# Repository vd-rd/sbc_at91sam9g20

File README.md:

# Microchip AT91SAM9G20

## Description
 The follow-up to my previous [SBC based on AT91SAM9260](https://github.com/vd-rd/sbc_at91sam9260), enhancing the board specs in computing power and flexibility. The board is smaller 60x40mm now (SAM9260 was 80x40mm) while keeping the same amount of supported RAM and interfaces. AT91SAM9G20 boosts core speed to 400MHz and bus speed to 133MHz.
 
Board overview (draft):
[TBD]

### Features

| Characteristic | Description |
| --- | --- |
| Dimensions | 60mm x 40mm |
| Processor | AT91SAM9G20 - ARM926EJ @ 400MHz |
| Oscillators |  18.432MHz main clock, 32.768kHz RTC |
| RAM | SDRAM 128MB max (2x512Mbit modules) |
| Storage | microSD |
| USB | 1 microUSB client, 2 USB Host|
| Ethernet | RMII header |
| WiFi/BT | N/A |
| Supply | USB 5V, ACIN 5V |

Common interfaces such as I2C, SPI, UART and GPIO are exposed on the header.

### Building and flashing

Build U-Boot and Linux kernel + rootFS - TBD

Flash to SDCard - TBD

### Resources

You can find all necesary information to build or evaluate the module here:
   - [Fabrication files](https://github.com/vd-rd/sbc_alw_a13/releases)

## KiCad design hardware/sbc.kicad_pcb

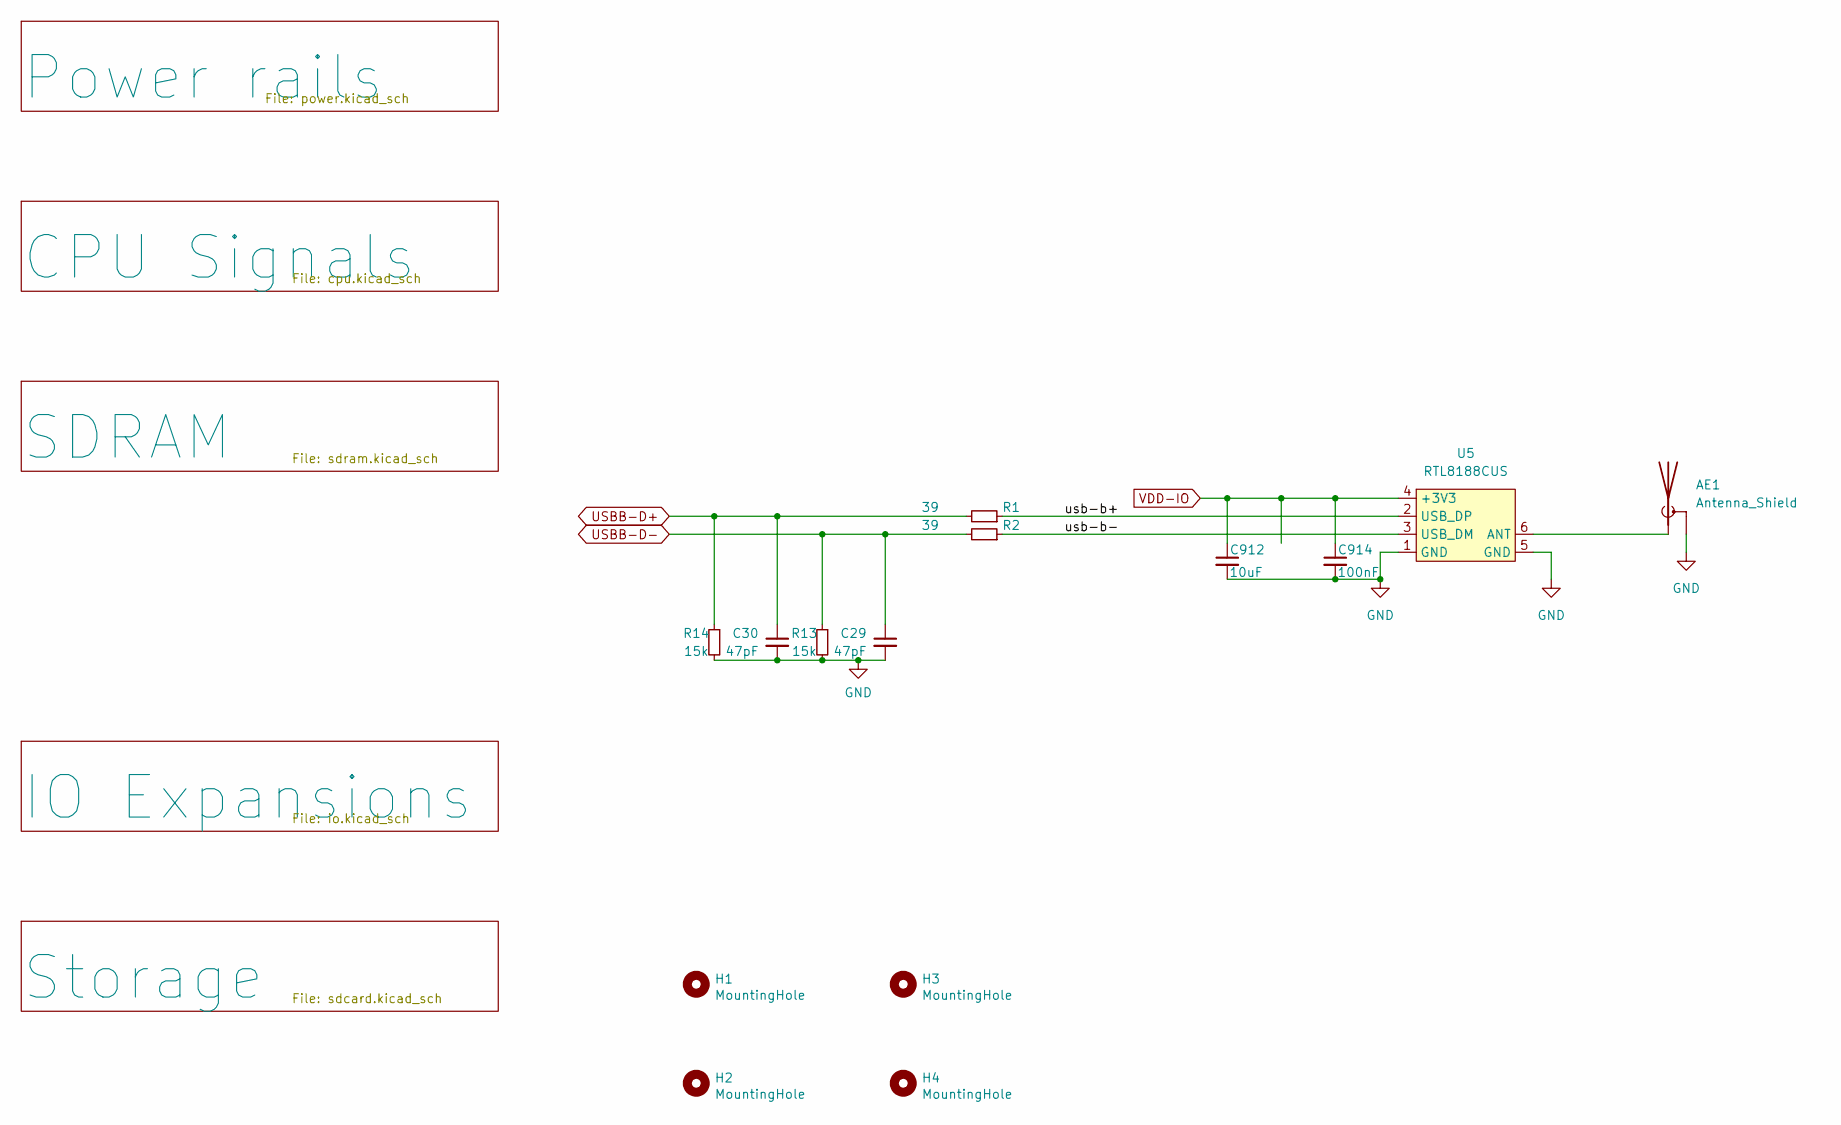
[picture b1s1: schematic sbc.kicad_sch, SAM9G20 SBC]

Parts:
AE1: Antenna_Shield; U.FL_Hirose_U.FL-R-SMT-1_Vertical
C29, C30: 47pF; C_0402_1005Metric
C912: 10uF; C_0603_1608Metric
C914: 100nF; C_0402_1005Metric
H1, H2, H3, H4: MountingHole; MountingHole_2.7mm_M2.5_DIN965
R1, R2: 39; R_0402_1005Metric
R13, R14: 15k; R_0402_1005Metric
U5: RTL8188CUS

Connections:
/usb-b+: R1.1, U5.2 (USB_DP)
/usb-b-: R2.1, U5.3 (USB_DM)
GND: AE1.2 (Shield), C29.2, C30.2, C912.2, C914.2, R13.2, R14.2, U5.1 (GND), U5.5 (GND); also elsewhere on the board
unnamed: AE1.1 (A), U5.6 (ANT)
USBB-D+: C30.1, R1.2, R14.1; also elsewhere on the board
USBB-D-: C29.1, R2.2, R13.1; also elsewhere on the board
VDD-IO: C912.1, C914.1, U5.4 (+3V3); also elsewhere on the board

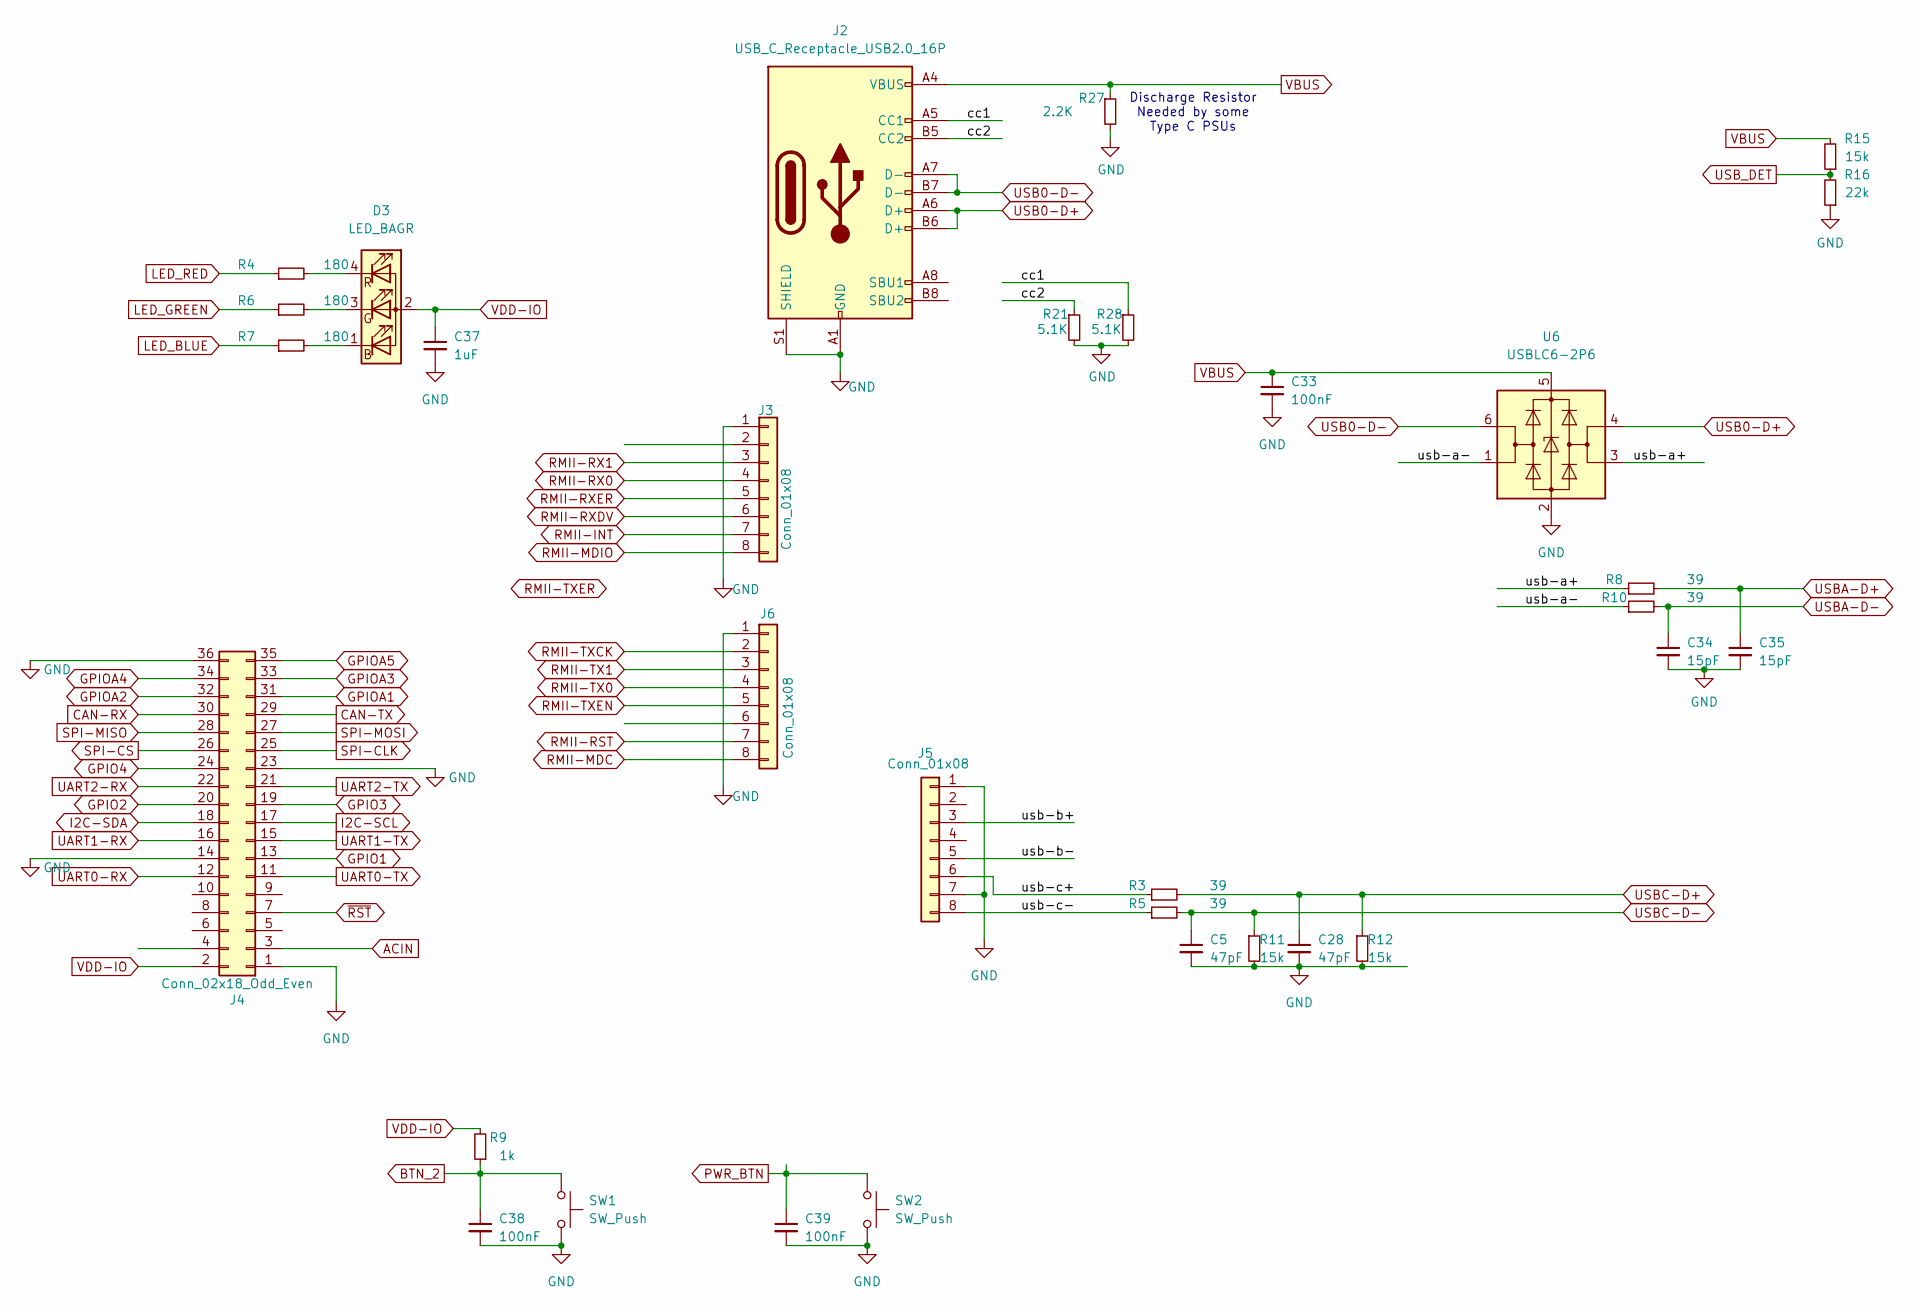
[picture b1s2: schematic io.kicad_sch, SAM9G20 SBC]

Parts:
C5, C28: 47pF; C_0402_1005Metric
C33, C38, C39: 100nF; C_0402_1005Metric
C34, C35: 15pF; C_0402_1005Metric
C37: 1uF; C_0402_1005Metric
D3: LED_BAGR; LED_RGB_Optosupply_OSTB0805C1E-A-0.8T
J2: USB_C_Receptacle_USB2.0_16P; USB_C_Receptacle_GCT_USB4105-xx-A_16P_TopMnt_Horizontal
J3, J5, J6: Conn_01x08; PinHeader_2x04_P1.27mm_Vertical
J4: Conn_02x18_Odd_Even; PinHeader_2x18_P2.54mm_Vertical
R3, R5, R8, R10: 39; R_0402_1005Metric
R4, R6, R7: 180; R_0402_1005Metric
R9: 1k; R_0402_1005Metric
R11, R12, R15: 15k; R_0402_1005Metric
R16: 22k; R_0402_1005Metric
R21, R28: 5.1K; R_0402_1005Metric; Part Description Resistor 2.2K M1005 1% 63mW
R27: 2.2K; R_0402_1005Metric; Part Description Resistor 2.2K M1005 1% 63mW
SW1, SW2: SW_Push; SW_SPST_EVQP7C
U6: USBLC6-2P6; SOT-23-6

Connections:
/IO Expansions/cc1: J2.A5 (CC1), R28.1
/IO Expansions/cc2: J2.B5 (CC2), R21.1
/IO Expansions/usb-a+: R8.1, U6.3 (I/O2)
/IO Expansions/usb-a-: R10.1, U6.1 (I/O1)
/IO Expansions/usb-b+: J5.3
/IO Expansions/usb-b-: J5.5
/IO Expansions/usb-c+: J5.6, R3.1
/IO Expansions/usb-c-: J5.8, R5.1
ACIN: J4.3; also elsewhere on the board
BTN_2: C38.1, R9.1, SW1.1; also elsewhere on the board
CAN-RX: J4.30
CAN-TX: J4.29
GND: C5.2, C28.2, C33.2, C34.2, C35.2, C37.2, C38.2, C39.2, J2.A1 (GND), J2.A12 (GND), J2.B1 (GND), J2.B12 (GND), J2.S1 (SHIELD), J3.1, J4.1, J4.14, J4.23, J4.36, J5.1, J5.7, J6.1, R11.2, R12.2, R16.1, R21.2, R27.2, R28.2, SW1.2, SW2.2, U6.2 (GND); also elsewhere on the board
GPIO1: J4.13; also elsewhere on the board
GPIO2: J4.20; also elsewhere on the board
GPIO3: J4.19; also elsewhere on the board
GPIO4: J4.24; also elsewhere on the board
GPIOA1: J4.31; also elsewhere on the board
GPIOA2: J4.32; also elsewhere on the board
GPIOA3: J4.33; also elsewhere on the board
GPIOA4: J4.34; also elsewhere on the board
GPIOA5: J4.35
I2C-SCL: J4.17; also elsewhere on the board
I2C-SDA: J4.18; also elsewhere on the board
LED_BLUE: R7.1; also elsewhere on the board
LED_GREEN: R6.1; also elsewhere on the board
LED_RED: R4.1; also elsewhere on the board
unnamed: D3.1 (BK), R7.2
unnamed: D3.3 (GK), R6.2
unnamed: D3.4 (RK), R4.2
PWR_BTN: C39.1, SW2.1; also elsewhere on the board
RMII-INT: J3.7
RMII-MDC: J6.8; also elsewhere on the board
RMII-MDIO: J3.8; also elsewhere on the board
RMII-RST: J6.7
RMII-RX0: J3.4; also elsewhere on the board
RMII-RX1: J3.3; also elsewhere on the board
RMII-RXDV: J3.6; also elsewhere on the board
RMII-RXER: J3.5; also elsewhere on the board
RMII-TX0: J6.4; also elsewhere on the board
RMII-TX1: J6.3; also elsewhere on the board
RMII-TXCK: J6.2; also elsewhere on the board
RMII-TXEN: J6.5; also elsewhere on the board
SPI-CLK: J4.25; also elsewhere on the board
SPI-CS: J4.26; also elsewhere on the board
SPI-MISO: J4.28; also elsewhere on the board
SPI-MOSI: J4.27; also elsewhere on the board
UART0-RX: J4.12; also elsewhere on the board
UART0-TX: J4.11; also elsewhere on the board
UART1-RX: J4.16; also elsewhere on the board
UART1-TX: J4.15; also elsewhere on the board
UART2-RX: J4.22; also elsewhere on the board
UART2-TX: J4.21; also elsewhere on the board
USB0-D+: J2.A6 (D+), J2.B6 (D+), U6.4 (I/O2)
USB0-D-: J2.A7 (D-), J2.B7 (D-), U6.6 (I/O1)
USBA-D+: C35.1, R8.2; also elsewhere on the board
USBA-D-: C34.1, R10.2; also elsewhere on the board
USBC-D+: C28.1, R3.2, R12.1; also elsewhere on the board
USBC-D-: C5.1, R5.2, R11.1; also elsewhere on the board
USB_DET: R15.1, R16.2; also elsewhere on the board
VBUS: C33.1, J2.A4 (VBUS), J2.A9 (VBUS), J2.B4 (VBUS), J2.B9 (VBUS), R15.2, R27.1, U6.5 (VBUS); also elsewhere on the board
VDD-IO: C37.1, D3.2 (A), J4.2, R9.2; also elsewhere on the board
~RST: J4.7; also elsewhere on the board

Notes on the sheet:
Discharge Resistor Needed by some Type C PSUs

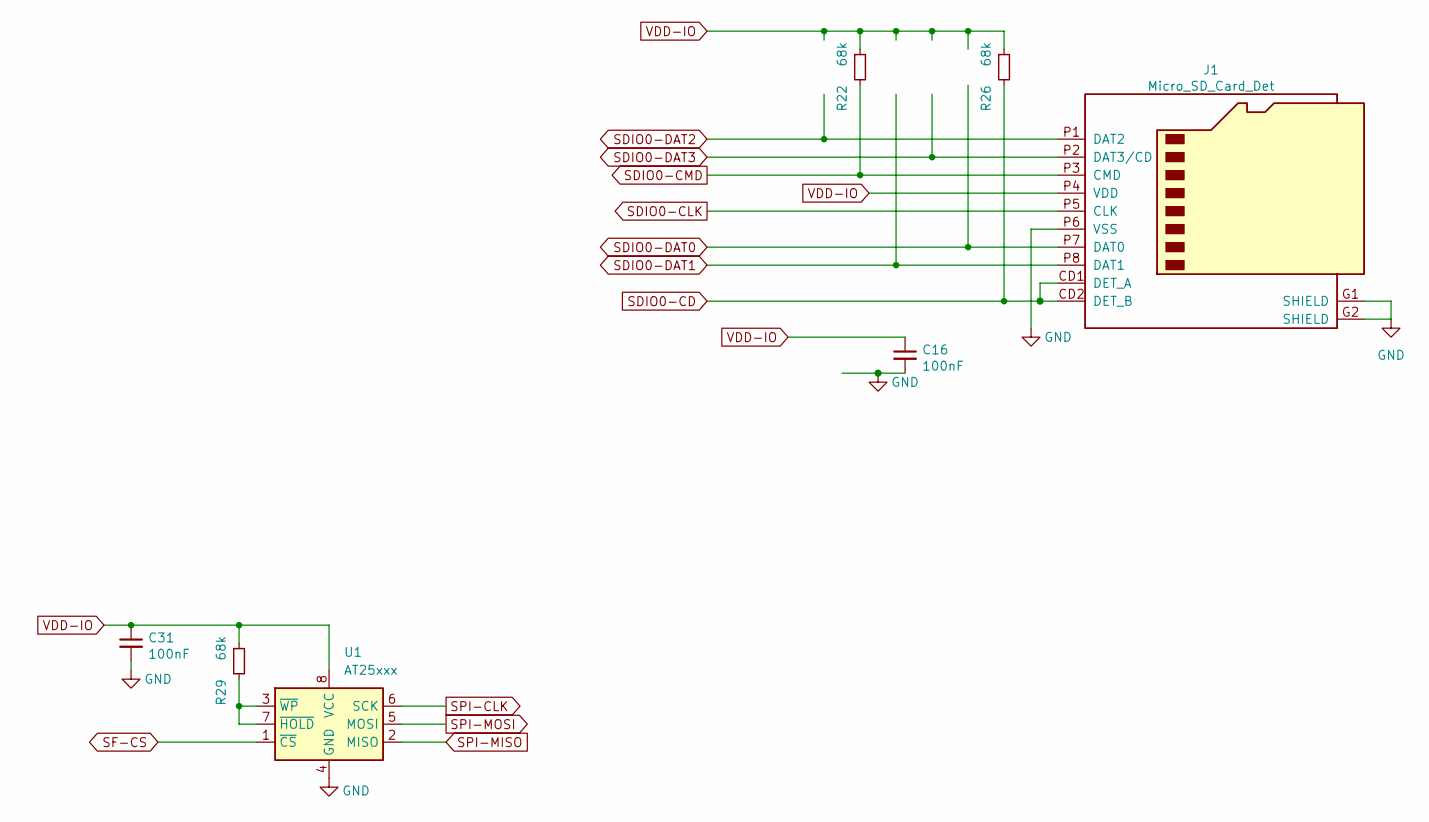
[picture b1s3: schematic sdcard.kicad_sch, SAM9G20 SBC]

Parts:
C16, C31: 100nF; C_0402_1005Metric
J1: Micro_SD_Card_Det; MEM20610118800A
R22, R26, R29: 68k; R_0402_1005Metric
U1: AT25xxx; SOIC-8_5.23x5.23mm_P1.27mm

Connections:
GND: C16.2, C31.2, J1.G1 (SHIELD), J1.G2 (SHIELD), J1.P6 (VSS), U1.4 (GND); also elsewhere on the board
unnamed: R29.2, U1.3 (~WP), U1.7 (~HOLD)
SDIO0-CD: J1.CD1 (DET_A), J1.CD2 (DET_B), R26.2; also elsewhere on the board
SDIO0-CLK: J1.P5 (CLK); also elsewhere on the board
SDIO0-CMD: J1.P3 (CMD), R22.2; also elsewhere on the board
SDIO0-DAT0: J1.P7 (DAT0); also elsewhere on the board
SDIO0-DAT1: J1.P8 (DAT1); also elsewhere on the board
SDIO0-DAT2: J1.P1 (DAT2); also elsewhere on the board
SDIO0-DAT3: J1.P2 (DAT3/CD); also elsewhere on the board
SF-CS: U1.1 (~CS); also elsewhere on the board
SPI-CLK: U1.6 (SCK); also elsewhere on the board
SPI-MISO: U1.2 (MISO); also elsewhere on the board
SPI-MOSI: U1.5 (MOSI); also elsewhere on the board
VDD-IO: C16.1, C31.1, J1.P4 (VDD), R22.1, R26.1, R29.1, U1.8 (VCC); also elsewhere on the board

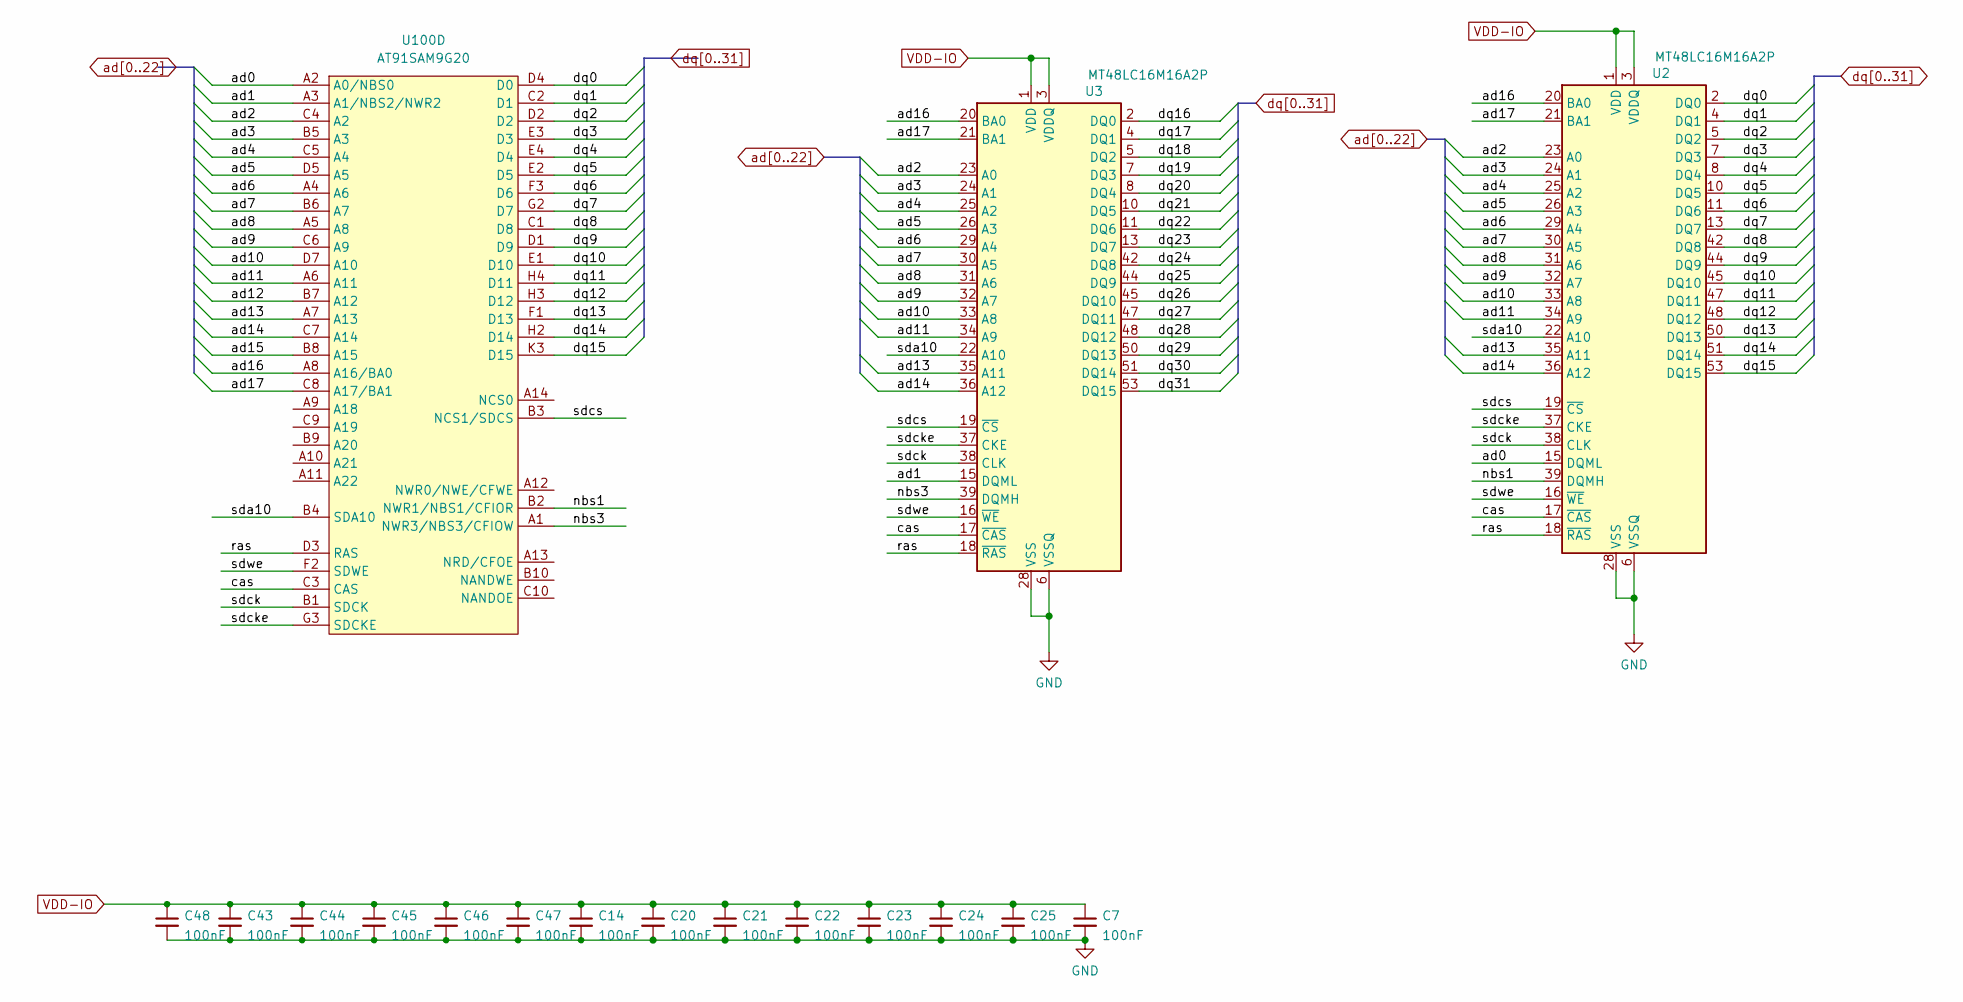
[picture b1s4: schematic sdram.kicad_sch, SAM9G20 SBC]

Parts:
C7, C14, C20, C21, C22, C23, C24, C25, C43, C44, C45, C46, C47, C48: 100nF; C_0402_1005Metric
U2, U3: MT48LC16M16A2P; TSOP-II-54_22.2x10.16mm_P0.8mm
U100: AT91SAM9G20; AT91SAM9G10

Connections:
/SDRAM/cas: U2.17 (~CAS), U3.17 (~CAS), U100.C3 (CAS)
/SDRAM/nbs1: U2.39 (DQMH), U100.B2 (NWR1/NBS1/CFIOR)
/SDRAM/nbs3: U3.39 (DQMH), U100.A1 (NWR3/NBS3/CFIOW)
/SDRAM/ras: U2.18 (~RAS), U3.18 (~RAS), U100.D3 (RAS)
/SDRAM/sda10: U2.22 (A10), U3.22 (A10), U100.B4 (SDA10)
/SDRAM/sdck: U2.38 (CLK), U3.38 (CLK), U100.B1 (SDCK)
/SDRAM/sdcke: U2.37 (CKE), U3.37 (CKE), U100.G3 (SDCKE)
/SDRAM/sdcs: U2.19 (~CS), U3.19 (~CS), U100.B3 (NCS1/SDCS)
/SDRAM/sdwe: U2.16 (~WE), U3.16 (~WE), U100.F2 (SDWE)
GND: C7.2, C14.2, C20.2, C21.2, C22.2, C23.2, C24.2, C25.2, C43.2, C44.2, C45.2, C46.2, C47.2, C48.2, U2.6 (VSSQ), U2.12 (VSSQ), U2.28 (VSS), U2.41 (VSS), U2.46 (VSSQ), U2.52 (VSSQ), U2.54 (VSS), U3.6 (VSSQ), U3.12 (VSSQ), U3.28 (VSS), U3.41 (VSS), U3.46 (VSSQ), U3.52 (VSSQ), U3.54 (VSS); also elsewhere on the board
VDD-IO: C7.1, C14.1, C20.1, C21.1, C22.1, C23.1, C24.1, C25.1, C43.1, C44.1, C45.1, C46.1, C47.1, C48.1, U2.1 (VDD), U2.3 (VDDQ), U2.9 (VDDQ), U2.14 (VDD), U2.27 (VDD), U2.43 (VDDQ), U2.49 (VDDQ), U3.1 (VDD), U3.3 (VDDQ), U3.9 (VDDQ), U3.14 (VDD), U3.27 (VDD), U3.43 (VDDQ), U3.49 (VDDQ); also elsewhere on the board
ad0: U2.15 (DQML), U100.A2 (A0/NBS0)
ad1: U3.15 (DQML), U100.A3 (A1/NBS2/NWR2)
ad2: U2.23 (A0), U3.23 (A0), U100.C4 (A2)
ad3: U2.24 (A1), U3.24 (A1), U100.B5 (A3)
ad4: U2.25 (A2), U3.25 (A2), U100.C5 (A4)
ad5: U2.26 (A3), U3.26 (A3), U100.D5 (A5)
ad6: U2.29 (A4), U3.29 (A4), U100.A4 (A6)
ad7: U2.30 (A5), U3.30 (A5), U100.B6 (A7)
ad8: U2.31 (A6), U3.31 (A6), U100.A5 (A8)
ad9: U2.32 (A7), U3.32 (A7), U100.C6 (A9)
ad10: U2.33 (A8), U3.33 (A8), U100.D7 (A10)
ad11: U2.34 (A9), U3.34 (A9), U100.A6 (A11)
ad12: U100.B7 (A12)
ad13: U2.35 (A11), U3.35 (A11), U100.A7 (A13)
ad14: U2.36 (A12), U3.36 (A12), U100.C7 (A14)
ad15: U100.B8 (A15)
ad16: U2.20 (BA0), U3.20 (BA0), U100.A8 (A16/BA0)
ad17: U2.21 (BA1), U3.21 (BA1), U100.C8 (A17/BA1)
dq0: U2.2 (DQ0), U100.D4 (D0)
dq1: U2.4 (DQ1), U100.C2 (D1)
dq2: U2.5 (DQ2), U100.D2
dq3: U2.7 (DQ3), U100.E3 (D3)
dq4: U2.8 (DQ4), U100.E4 (D4)
dq5: U2.10 (DQ5), U100.E2 (D5)
dq6: U2.11 (DQ6), U100.F3 (D6)
dq7: U2.13 (DQ7), U100.G2 (D7)
dq8: U2.42 (DQ8), U100.C1 (D8)
dq9: U2.44 (DQ9), U100.D1 (D9)
dq10: U2.45 (DQ10), U100.E1 (D10)
dq11: U2.47 (DQ11), U100.H4 (D11)
dq12: U2.48 (DQ12), U100.H3 (D12)
dq13: U2.50 (DQ13), U100.F1 (D13)
dq14: U2.51 (DQ14), U100.H2 (D14)
dq15: U2.53 (DQ15), U100.K3 (D15)
dq16: U3.2 (DQ0); also elsewhere on the board
dq17: U3.4 (DQ1); also elsewhere on the board
dq18: U3.5 (DQ2); also elsewhere on the board
dq19: U3.7 (DQ3); also elsewhere on the board
dq20: U3.8 (DQ4); also elsewhere on the board
dq21: U3.10 (DQ5); also elsewhere on the board
dq22: U3.11 (DQ6); also elsewhere on the board
dq23: U3.13 (DQ7); also elsewhere on the board
dq24: U3.42 (DQ8); also elsewhere on the board
dq25: U3.44 (DQ9); also elsewhere on the board
dq26: U3.45 (DQ10); also elsewhere on the board
dq27: U3.47 (DQ11); also elsewhere on the board
dq28: U3.48 (DQ12); also elsewhere on the board
dq29: U3.50 (DQ13); also elsewhere on the board
dq30: U3.51 (DQ14); also elsewhere on the board
dq31: U3.53 (DQ15); also elsewhere on the board

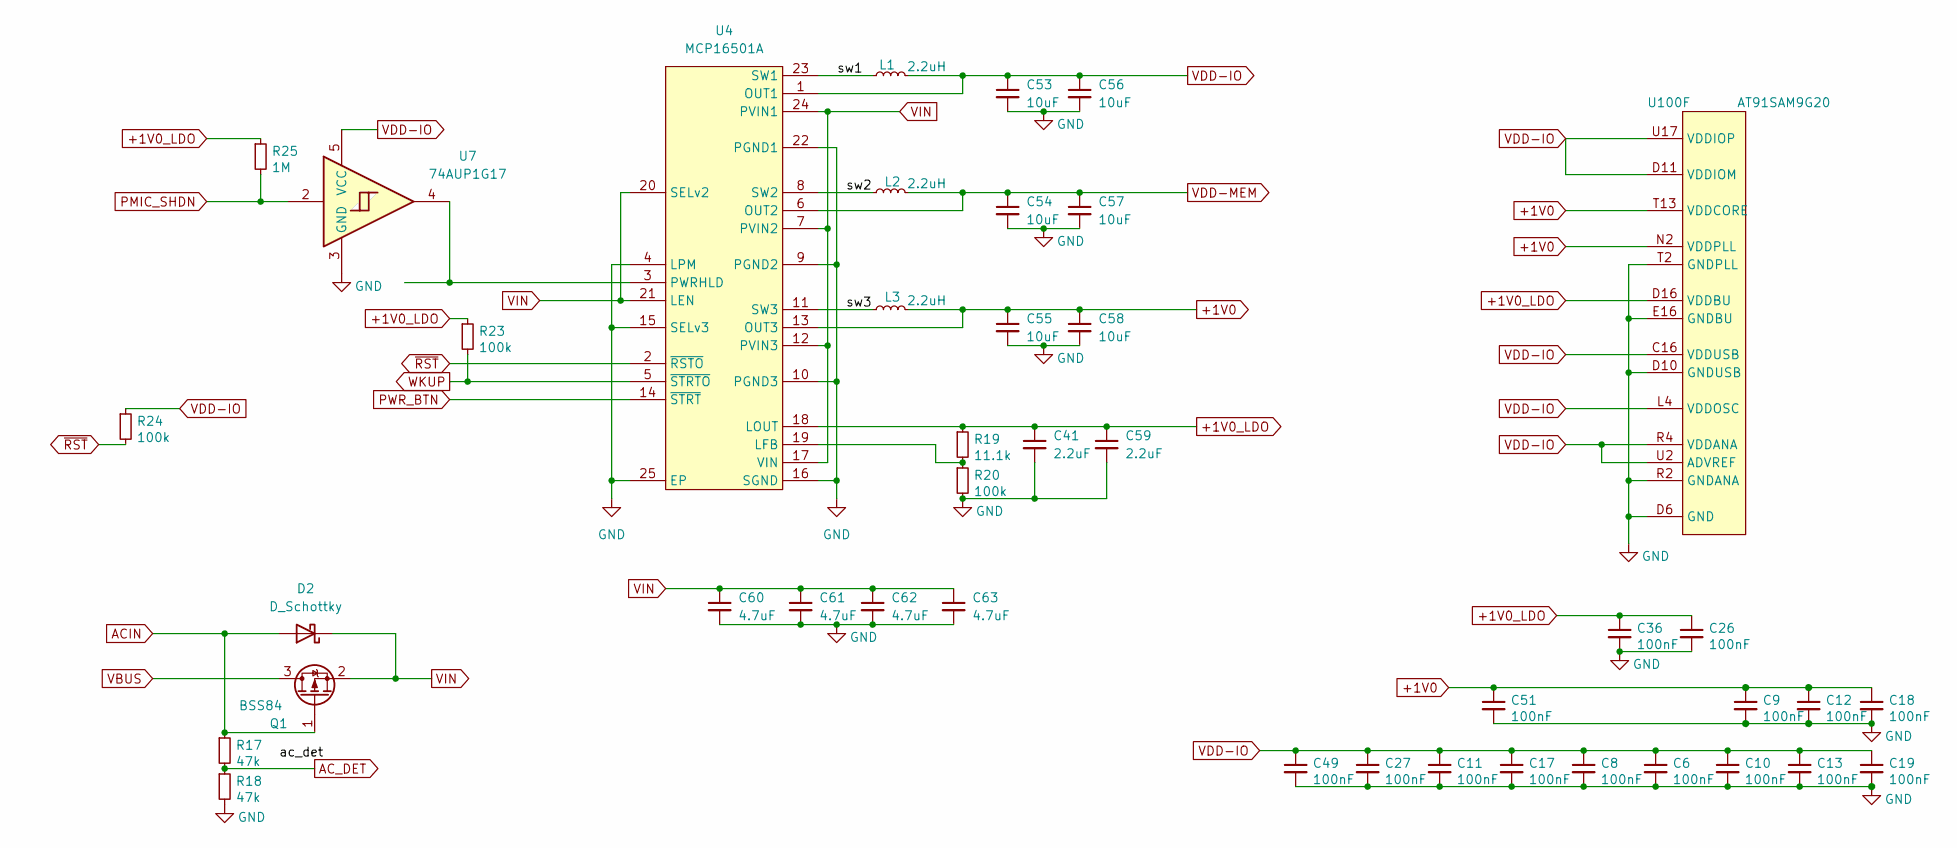
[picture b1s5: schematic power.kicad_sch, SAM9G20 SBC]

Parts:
C6, C8, C9, C10, C11, C12, C13, C17, C18, C19, C26, C27, C36, C49, C51: 100nF; C_0402_1005Metric
C41, C59: 2.2uF; C_0402_1005Metric
C53, C54, C55, C56, C57, C58: 10uF; C_0603_1608Metric
C60, C61, C62, C63: 4.7uF; C_0603_1608Metric
D2: D_Schottky; D_SOD-323
L1, L2, L3: 2.2uH; L_Wuerth_MAPI-2512
Q1: BSS84; SOT-323_SC-70
R17, R18: 47k; R_0402_1005Metric
R19: 11.1k; R_0402_1005Metric
R20, R23, R24: 100k; R_0402_1005Metric
R25: 1M; R_0402_1005Metric
U4: MCP16501A; QFN-24-1EP_4x4mm_P0.5mm_EP2.7x2.7mm_ThermalVias
U7: 74AUP1G17; Texas_R-PDSO-N5_DRL-5
U100: AT91SAM9G20; AT91SAM9G10

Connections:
+1V0: C9.1, C12.1, C18.1, C51.1, C55.1, C58.1, L3.2, U4.13 (OUT3), U100.D9 (VDDCORE), U100.H14 (VDDCORE), U100.M1 (VDDCORE), U100.N2 (VDDPLL), U100.P2 (VDDPLL), U100.T13 (VDDCORE)
+1V0_LDO: C26.1, C36.1, C41.1, C59.1, R19.1, R23.1, R25.1, U4.18 (LOUT), U100.D16 (VDDBU); also elsewhere on the board
/Power rails/sw1: L1.1, U4.23 (SW1)
/Power rails/sw2: L2.1, U4.8 (SW2)
/Power rails/sw3: L3.1, U4.11 (SW3)
ACIN: D2.2 (A), Q1.1 (G), R17.1; also elsewhere on the board
AC_DET: R17.2, R18.1; also elsewhere on the board
GND: C6.2, C8.2, C9.2, C10.2, C11.2, C12.2, C13.2, C17.2, C18.2, C19.2, C26.2, C27.2, C36.2, C41.2, C49.2, C51.2, C53.2, C54.2, C55.2, C56.2, C57.2, C58.2, C59.2, C60.2, C61.2, C62.2, C63.2, R18.2, R20.2, U4.4 (LPM), U4.9 (PGND2), U4.10 (PGND3), U4.15 (SELv3), U4.16 (SGND), U4.22 (PGND1), U4.25 (EP), U7.3 (GND), U100.D6 (GND), U100.D8 (GND), U100.D10 (GNDUSB), U100.D12 (GNDUSB), U100.E16 (GNDBU), U100.F4 (GND), U100.G14 (GND), U100.H8 (GND), U100.H9 (GND), U100.H10 (GND), U100.J8 (GND), U100.J9 (GND), U100.J10 (GND), U100.K8 (GND), U100.K9 (GND), U100.K10 (GND), U100.K16 (GND), U100.L1 (GND), U100.M3 (GND), U100.R2 (GNDANA), U100.R7 (GND), U100.T2 (GNDPLL), U100.T7 (GND), U100.T15 (GND), U100.U1 (GNDPLL); also elsewhere on the board
unnamed: R19.2, R20.1, U4.19 (LFB)
unnamed: U4.3 (PWRHLD), U7.4
PMIC_SHDN: R25.2, U7.2; also elsewhere on the board
PWR_BTN: U4.14 (~STRT); also elsewhere on the board
VBUS: Q1.3 (D); also elsewhere on the board
VDD-IO: C6.1, C8.1, C10.1, C11.1, C13.1, C17.1, C19.1, C27.1, C49.1, C53.1, C56.1, L1.2, R24.1, U4.1 (OUT1), U7.5 (VCC), U100.C16 (VDDUSB), U100.D11 (VDDIOM), U100.G4 (VDDIOM), U100.J3 (VDDIOM), U100.L4 (VDDOSC), U100.P8 (VDDIOP), U100.R4 (VDDANA), U100.U2 (ADVREF), U100.U17 (VDDIOP); also elsewhere on the board
VDD-MEM: C54.1, C57.1, L2.2, U4.6 (OUT2)
VIN: C60.1, C61.1, C62.1, C63.1, D2.1 (K), Q1.2 (S), U4.7 (PVIN2), U4.12 (PVIN3), U4.17 (VIN), U4.20 (SELv2), U4.21 (LEN), U4.24 (PVIN1)
WKUP: R23.2, U4.5 (~STRTO); also elsewhere on the board
~RST: R24.2, U4.2 (~RSTO); also elsewhere on the board

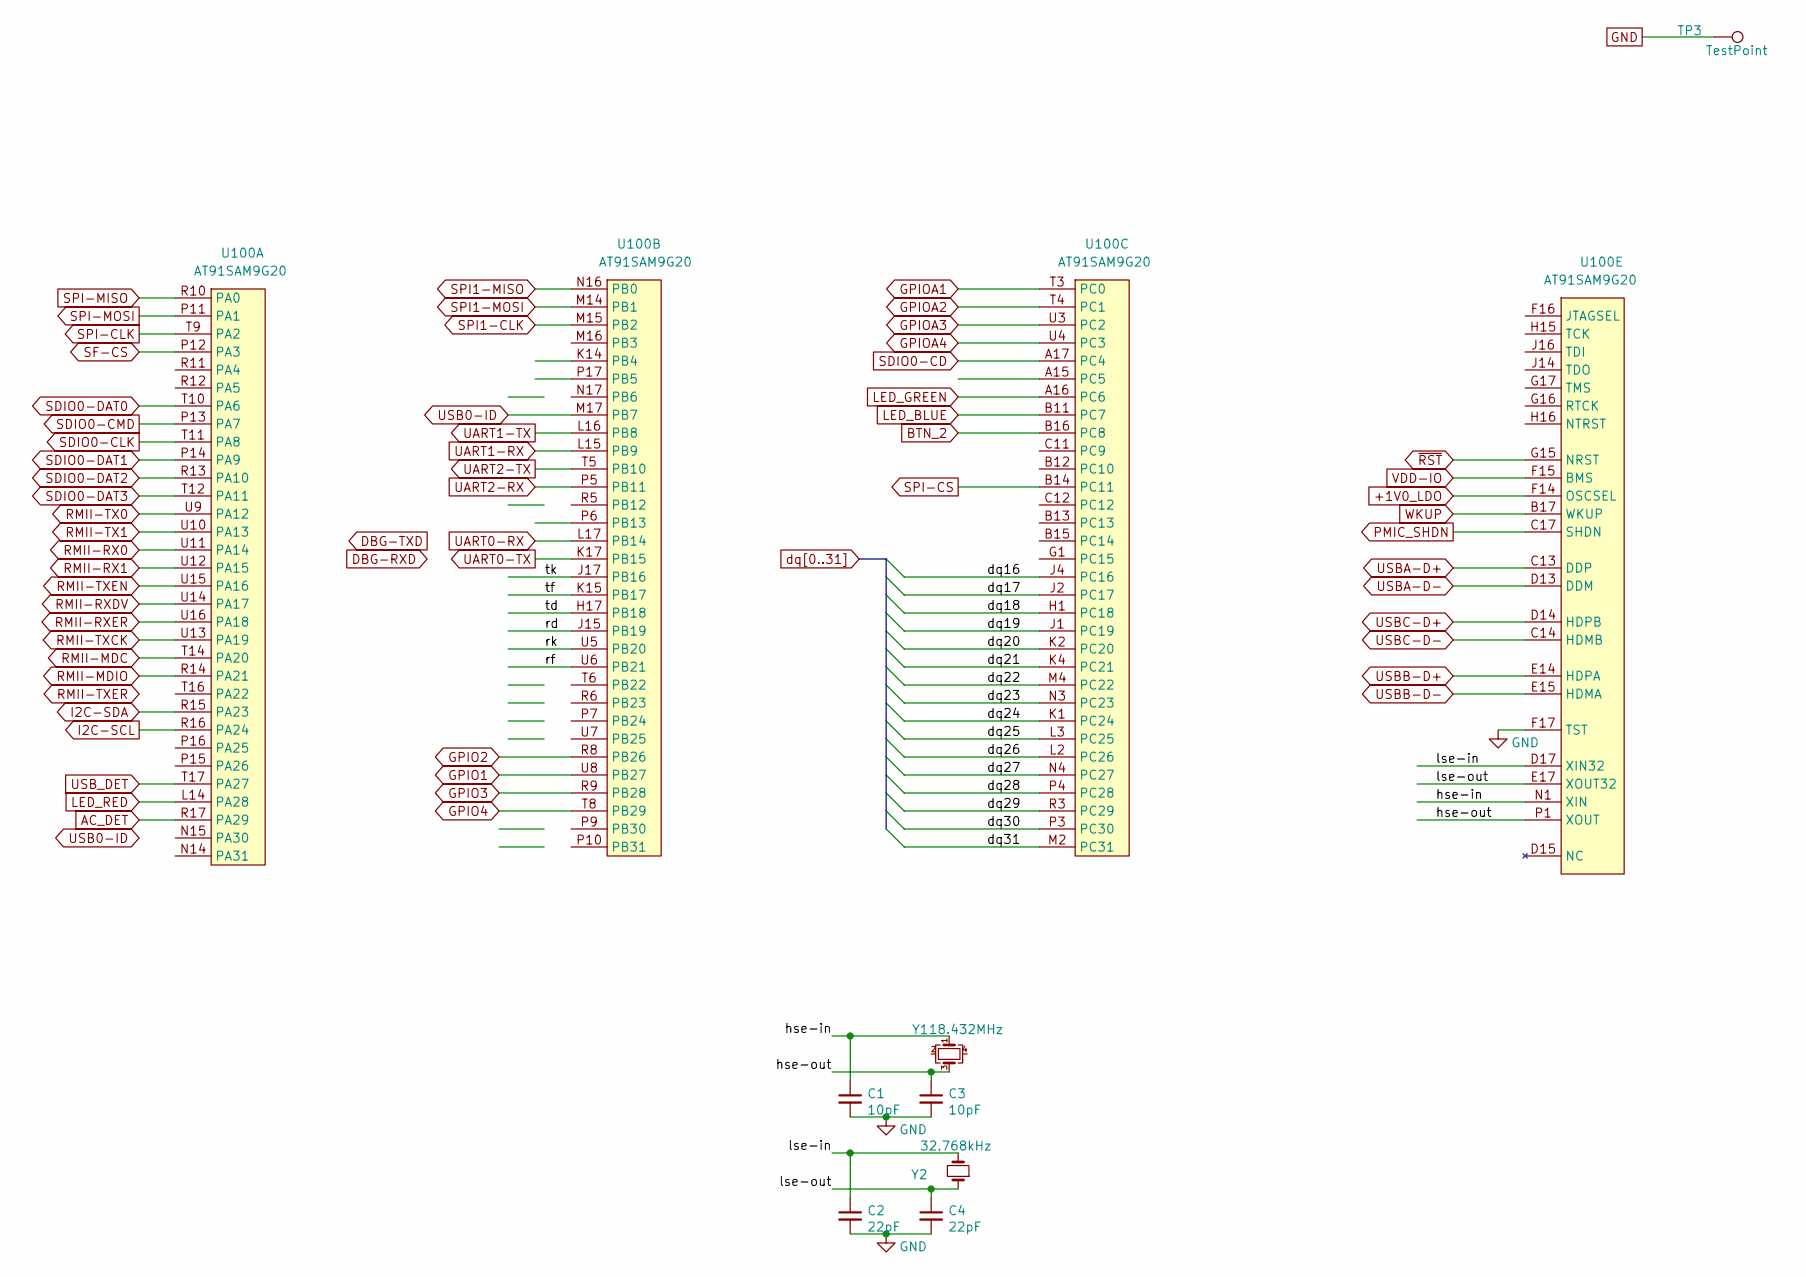
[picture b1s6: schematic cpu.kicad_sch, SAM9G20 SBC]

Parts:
C1, C3: 10pF; C_0402_1005Metric
C2, C4: 22pF; C_0402_1005Metric
TP3: TestPoint; TestPoint_Pad_D1.0mm
U100: AT91SAM9G20; AT91SAM9G10
Y1: 18.432MHz; Crystal_SMD_3225-4Pin_3.2x2.5mm
Y2: 32.768kHz; Crystal_SMD_3215-2Pin_3.2x1.5mm

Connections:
+1V0_LDO: U100.F14 (OSCSEL); also elsewhere on the board
/CPU Signals/hse-in: C1.1, U100.N1 (XIN), Y1.1
/CPU Signals/hse-out: C3.1, U100.P1 (XOUT), Y1.3
/CPU Signals/lse-in: C2.1, U100.D17 (XIN32), Y2.2
/CPU Signals/lse-out: C4.1, U100.E17 (XOUT32), Y2.1
/CPU Signals/rd: U100.J15 (PB19)
/CPU Signals/rf: U100.U6 (PB21)
/CPU Signals/rk: U100.U5 (PB20)
/CPU Signals/td: U100.H17 (PB18)
/CPU Signals/tf: U100.K15 (PB17)
/CPU Signals/tk: U100.J17 (PB16)
AC_DET: U100.R17 (PA29); also elsewhere on the board
BTN_2: U100.B16 (PC8); also elsewhere on the board
GND: C1.2, C2.2, C3.2, C4.2, TP3.1 (1_1), U100.F17 (TST); also elsewhere on the board
GPIO1: U100.U8 (PB27); also elsewhere on the board
GPIO2: U100.R8 (PB26); also elsewhere on the board
GPIO3: U100.R9 (PB28); also elsewhere on the board
GPIO4: U100.T8 (PB29); also elsewhere on the board
GPIOA1: U100.T3 (PC0); also elsewhere on the board
GPIOA2: U100.T4 (PC1); also elsewhere on the board
GPIOA3: U100.U3 (PC2); also elsewhere on the board
GPIOA4: U100.U4 (PC3); also elsewhere on the board
I2C-SCL: U100.R16 (PA24); also elsewhere on the board
I2C-SDA: U100.R15 (PA23); also elsewhere on the board
LED_BLUE: U100.B11 (PC7); also elsewhere on the board
LED_GREEN: U100.A16 (PC6); also elsewhere on the board
LED_RED: U100.L14 (PA28); also elsewhere on the board
PMIC_SHDN: U100.C17 (SHDN); also elsewhere on the board
RMII-MDC: U100.T14 (PA20); also elsewhere on the board
RMII-MDIO: U100.R14 (PA21); also elsewhere on the board
RMII-RX0: U100.U11 (PA14); also elsewhere on the board
RMII-RX1: U100.U12 (PA15); also elsewhere on the board
RMII-RXDV: U100.U14 (PA17); also elsewhere on the board
RMII-RXER: U100.U16 (PA18); also elsewhere on the board
RMII-TX0: U100.U9 (PA12); also elsewhere on the board
RMII-TX1: U100.U10 (PA13); also elsewhere on the board
RMII-TXCK: U100.U13 (PA19); also elsewhere on the board
RMII-TXEN: U100.U15 (PA16); also elsewhere on the board
SDIO0-CD: U100.A17 (PC4); also elsewhere on the board
SDIO0-CLK: U100.T11 (PA8); also elsewhere on the board
SDIO0-CMD: U100.P13 (PA7); also elsewhere on the board
SDIO0-DAT0: U100.T10 (PA6); also elsewhere on the board
SDIO0-DAT1: U100.P14 (PA9); also elsewhere on the board
SDIO0-DAT2: U100.R13 (PA10); also elsewhere on the board
SDIO0-DAT3: U100.T12 (PA11); also elsewhere on the board
SF-CS: U100.P12 (PA3); also elsewhere on the board
SPI1-CLK: U100.M15 (PB2)
SPI1-MISO: U100.N16 (PB0)
SPI1-MOSI: U100.M14 (PB1)
SPI-CLK: U100.T9 (PA2); also elsewhere on the board
SPI-CS: U100.B14 (PC11); also elsewhere on the board
SPI-MISO: U100.R10 (PA0); also elsewhere on the board
SPI-MOSI: U100.P11 (PA1); also elsewhere on the board
UART0-RX: U100.L17 (PB14); also elsewhere on the board
UART0-TX: U100.K17 (PB15); also elsewhere on the board
UART1-RX: U100.L15 (PB9); also elsewhere on the board
UART1-TX: U100.L16 (PB8); also elsewhere on the board
UART2-RX: U100.P5 (PB11); also elsewhere on the board
UART2-TX: U100.T5 (PB10); also elsewhere on the board
USB0-ID: U100.M17 (PB7)
USBA-D+: U100.C13 (DDP); also elsewhere on the board
USBA-D-: U100.D13 (DDM); also elsewhere on the board
USBB-D+: U100.E14 (HDPA); also elsewhere on the board
USBB-D-: U100.E15 (HDMA); also elsewhere on the board
USBC-D+: U100.D14 (HDPB); also elsewhere on the board
USBC-D-: U100.C14 (HDMB); also elsewhere on the board
USB_DET: U100.T17 (PA27); also elsewhere on the board
VDD-IO: U100.F15 (BMS); also elsewhere on the board
WKUP: U100.B17 (WKUP); also elsewhere on the board
dq16: U100.J4 (PC16); also elsewhere on the board
dq17: U100.J2 (PC17); also elsewhere on the board
dq18: U100.H1 (PC18); also elsewhere on the board
dq19: U100.J1 (PC19); also elsewhere on the board
dq20: U100.K2 (PC20); also elsewhere on the board
dq21: U100.K4 (PC21); also elsewhere on the board
dq22: U100.M4 (PC22); also elsewhere on the board
dq23: U100.N3 (PC23); also elsewhere on the board
dq24: U100.K1 (PC24); also elsewhere on the board
dq25: U100.L3 (PC25); also elsewhere on the board
dq26: U100.L2 (PC26); also elsewhere on the board
dq27: U100.N4 (PC27); also elsewhere on the board
dq28: U100.P4 (PC28); also elsewhere on the board
dq29: U100.R3 (PC29); also elsewhere on the board
dq30: U100.P3 (PC30); also elsewhere on the board
dq31: U100.M2 (PC31); also elsewhere on the board
~RST: U100.G15 (NRST); also elsewhere on the board

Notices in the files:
hardware/sbc.kicad_pcb:
© VDRD
